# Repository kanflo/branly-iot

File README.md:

# Branly IoT

"Branly" is the name given to my personal adventure into the world of IoT. [Édouard Branly](https://en.wikipedia.org/wiki/Édouard_Branly) was one of the early pioneers in wireless telegraphy. This project will span everything between software design/architecture and hardware design.

This git holds the following:

* [hardware](https://github.com/kanflo/branly-iot/hardware) is my first steps at designing hardware. In this case an RFM69 based modem for the RaspberryPi. There is one SMT version and one "through hole" version that most should be able to solder. The zip files contains the gerbers.
* [BranlyPi modem](https://github.com/kanflo/branly-iot/branly_pi_modem) is Arduino based software for the above hardware.
* [Branly node](https://github.com/kanflo/branly-iot/branly_node) is an Arduino node that talks to the BranlPi modem.
* [Branly Gateway](https://github.com/kanflo/branly-iot/branly-gateway) is a gateway that receives data from the BranlyPi modem and posts it to EmonCMS.

This code is accompanied by a series of [blog posts](http://johan.kanflo.com/meet-the-branly-iot-platform/).

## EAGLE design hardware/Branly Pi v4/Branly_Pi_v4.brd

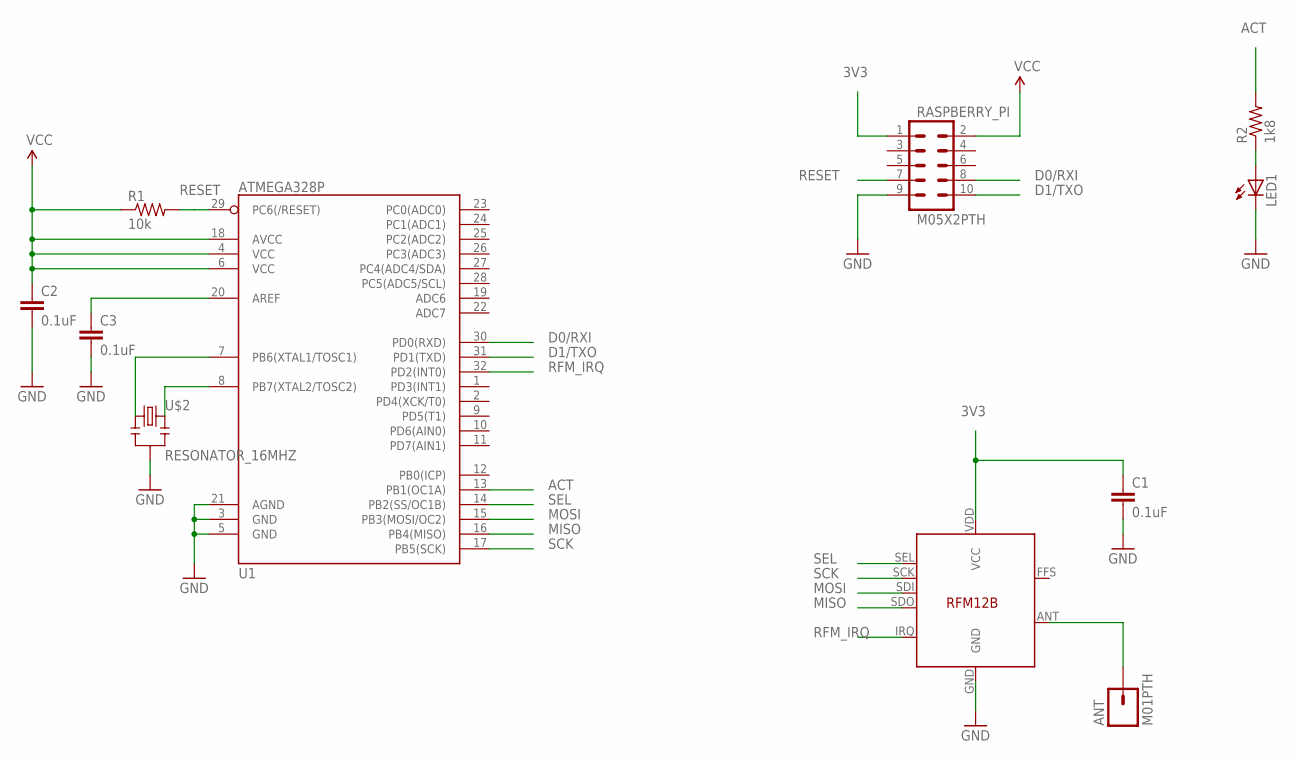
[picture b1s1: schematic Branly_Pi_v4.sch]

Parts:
ANT: M01PTH; 1X01
C1, C2, C3: 0.1uF; 0603-CAP
LED1: LED0603; LED-0603
R1: 10k; 0603-RES
R2: 1k8; 0603-RES
RASPBERRY_PI: M05X2PTH; AVR_ICSP
U1: ATMEGA328P; TQFP32-08
U2: RFM12B
U$2: RESONATOR_16MHZ; RESONATOR_SMD

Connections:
3V3: C1.1, RASPBERRY_PI.1, U2.VDD (VCC)
ACT: R2.2, U1.13 (PB1(OC1A))
D0/RXI: RASPBERRY_PI.8, U1.30 (PD0(RXD))
D1/TXO: RASPBERRY_PI.10, U1.31 (PD1(TXD))
GND: C1.2, C2.2, C3.2, LED1.C, RASPBERRY_PI.9, U1.3 (GND), U1.5 (GND), U1.21 (AGND), U2.GND, U$2.2
MISO: U1.16 (PB4(MISO)), U2.SDO
MOSI: U1.15 (PB3(MOSI/OC2)), U2.SDI
unnamed: LED1.A, R2.1
unnamed: C3.1, U1.20 (AREF)
unnamed: U1.7 (PB6(XTAL1/TOSC1)), U$2.1
unnamed: U1.8 (PB7(XTAL2/TOSC2)), U$2.3
unnamed: ANT.1, U2.ANT
RESET: R1.2, RASPBERRY_PI.7, U1.29 (PC6(/RESET))
RFM_IRQ: U1.32 (PD2(INT0)), U2.IRQ
SCK: U1.17 (PB5(SCK)), U2.SCK
SEL: U1.14 (PB2(SS/OC1B)), U2.SEL
VCC: C2.1, R1.1, RASPBERRY_PI.2, U1.4 (VCC), U1.6 (VCC), U1.18 (AVCC)

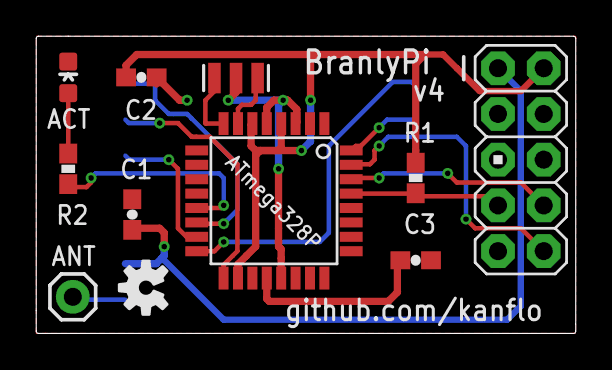
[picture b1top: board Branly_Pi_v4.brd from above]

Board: 2 copper layers, 30.0 x 16.5 mm, 12 parts (1 on the bottom side), 17 nets.

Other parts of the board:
U$3: OSHW-LOGO-S

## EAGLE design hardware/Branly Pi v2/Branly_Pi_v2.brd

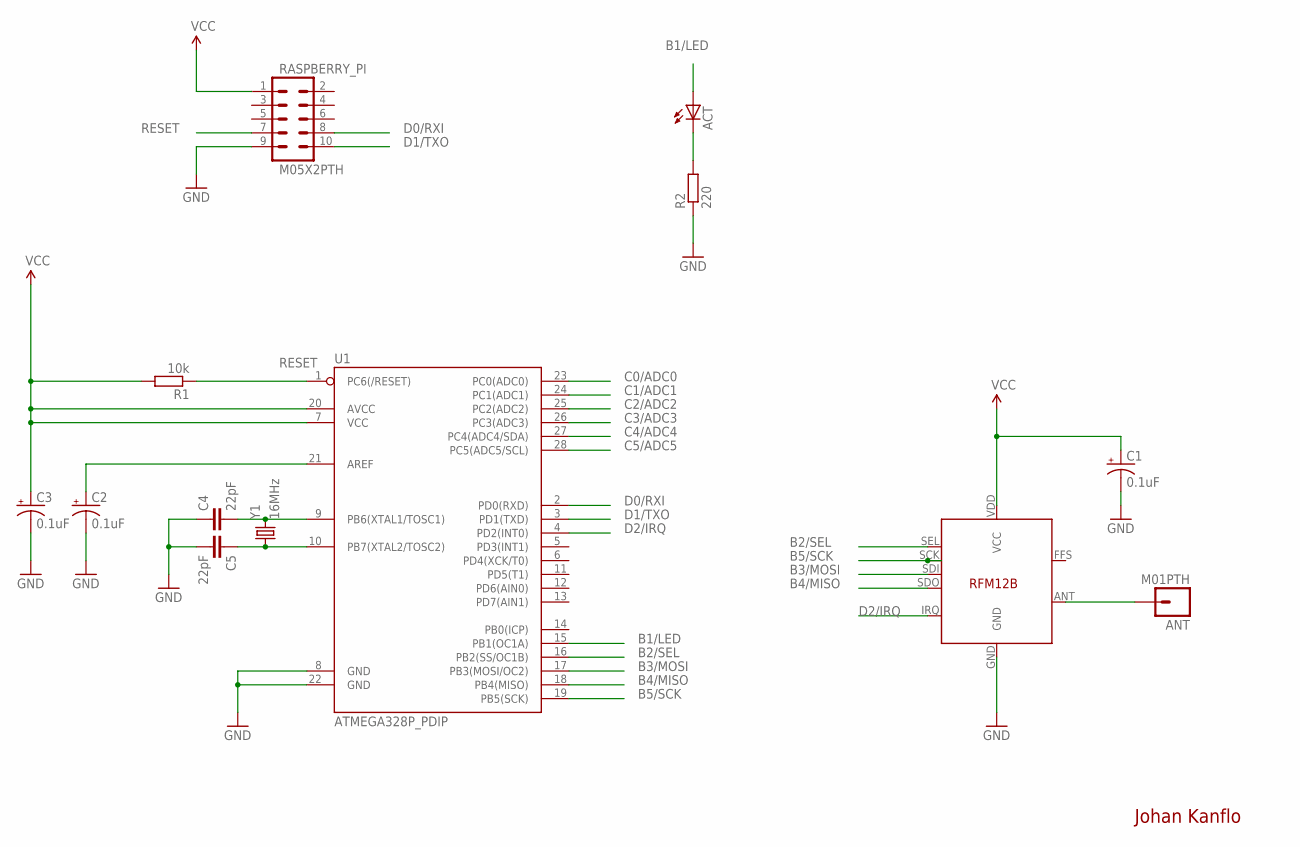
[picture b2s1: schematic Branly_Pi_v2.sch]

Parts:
ACT: LED5MM
ANT: M01PTH; 1X01
C1, C2, C3: 0.1uF; CPOL-RADIAL-10UF-25V
C4, C5: 22pF; CAP-PTH-SMALL2
R1: 10k; 0207/7
R2: 220; 0207/7
RASPBERRY_PI: M05X2PTH; AVR_ICSP
U1: ATMEGA328P_PDIP; DIL28-3
U2: RFM12B
Y1: 16MHz; HC49US

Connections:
ACT: ACT.K (C), R2.2
B1/LED: ACT.A, U1.15 (PB1(OC1A))
B2/SEL: U1.16 (PB2(SS/OC1B)), U2.SEL
B3/MOSI: U1.17 (PB3(MOSI/OC2)), U2.SDI
B4/MISO: U1.18 (PB4(MISO)), U2.SDO
B5/SCK: U1.19 (PB5(SCK)), U2.SCK
C0/ADC0: U1.23 (PC0(ADC0))
C1/ADC1: U1.24 (PC1(ADC1))
C2/ADC2: U1.25 (PC2(ADC2))
C3/ADC3: U1.26 (PC3(ADC3))
C4/ADC4: U1.27 (PC4(ADC4/SDA))
C5/ADC5: U1.28 (PC5(ADC5/SCL))
D0/RXI: RASPBERRY_PI.8, U1.2 (PD0(RXD))
D1/TXO: RASPBERRY_PI.10, U1.3 (PD1(TXD))
D2/IRQ: U1.4 (PD2(INT0)), U2.IRQ
GND: C1.2 (-), C2.2 (-), C3.2 (-), C4.1, C5.2, R2.1, RASPBERRY_PI.9, U1.8 (GND), U1.22 (GND), U2.GND
unnamed: C4.2, U1.9 (PB6(XTAL1/TOSC1)), Y1.2
unnamed: C2.1 (+), U1.21 (AREF)
unnamed: C5.1, U1.10 (PB7(XTAL2/TOSC2)), Y1.1
unnamed: ANT.1, U2.ANT
RESET: R1.1, RASPBERRY_PI.7, U1.1 (PC6(/RESET))
VCC: C1.1 (+), C3.1 (+), R1.2, RASPBERRY_PI.1, U1.7 (VCC), U1.20 (AVCC), U2.VDD (VCC)

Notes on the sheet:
Johan Kanflo

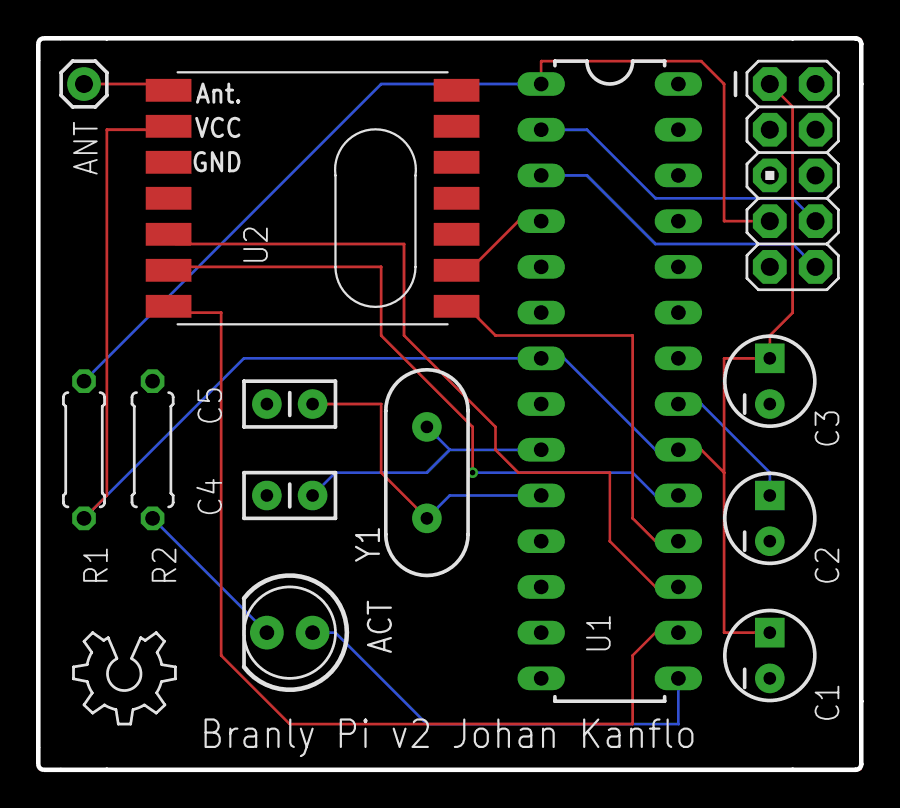
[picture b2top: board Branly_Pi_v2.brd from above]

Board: 2 copper layers, 45.7 x 40.6 mm, 14 parts (0 on the bottom side), 16 nets.

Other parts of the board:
U$3: OSHW_6X200_NOTEXT

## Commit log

2015-11-09 Added BranlyPi HW
2015-11-09 Initial SW. Node, modem and gateway
2015-11-09 Added note about gerbers.
2015-11-12 Added link to blog post.
2023-12-14 Added Branly Arduino Library

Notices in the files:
parts and their libraries:
SparkFun-DigitalIC: Licensing: CC v3.0 Share-Alike You are welcome to use this library for commercial purposes.
SparkFun-Connectors: Licensing: Creative Commons ShareAlike 4.0 International - https://creativecommons.org/licenses/by-sa/4.0
